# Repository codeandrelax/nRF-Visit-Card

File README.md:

# Bluetooth Compass Project

This project is a personal showcase of my skills in **PCB design, embedded firmware development, and Android application programming**—centered around a custom-built **Bluetooth-enabled digital compass**.

I created this project as a demonstration of my capability to design and manufacture a clean, self-contained PCB solution, free from the reliance on off-the-shelf BLE modules. It’s a manifestation of my passion for building systems from scratch, with a focus on RF design and embedded software.

---

## 🛠️ Hardware Overview

- **Microcontroller**: Nordic nRF52832 with integrated BLE support  
- **Antenna**: Custom-designed **meandering line antenna** tuned to **2.4 GHz**  
- **Magnetometer**: QMC5883L for 3-axis magnetic field sensing (I2C communication)  
- **LEDs**:  
  - 12x Blue LEDs in a circular layout to represent compass directions  
  - 6x Status LEDs: USER, CONNECTIVITY INDICATOR, HEARTBEAT  
- **Battery**: CR2032 coin cell slot  
- **Programming Interface**: SWD (SWCLK, SWDIO), UART connector  
- **Clock**: 32 MHz external crystal for BLE SoftDevice  
- **PCB Stack**: 4-layer custom design, credit-card sized  

> The reset pin is repurposed as a **user input button**. The reset functionality is disabled in software to allow this.

---

## 🔧 Firmware Overview

Firmware is built on **Zephyr RTOS**, enabling modular and modern embedded software design.

A **custom Bluetooth service**, `CompassService`, is implemented, exposing three key characteristics:

1. **Button State**  
2. **User LED Control**  
3. **Direction Output**

### 📡 Magnetometer Integration

- QMC5883L communicates over I2C.  
- Each axis (X, Y, Z) is read as a signed 16-bit value:

```c
int16_t value = (MSB << 8) | LSB;
```

- Orientation is calculated using the X and Y components:

```c
float angle_rad = atan2f((float)mag_y, (float)mag_x);
float angle_deg = angle_rad * (180.0f / M_PI);
if (angle_deg < 0) angle_deg += 360.0f;
```

The direction value is then:
- **Broadcast over BLE** using notify characteristics  
- **Rendered via LEDs** in a circular fashion to act as a real-time compass  

The system runs on the **internal RC oscillator**, while the **external crystal is reserved for BLE operations**.

---

## 📱 Android App Overview

Developed using **Android Studio**, the app uses the **Processing library** to render a dynamic compass needle.

- **BLE scanning** locates the `BluetoothCompass`  
- On connection, the app:  
  - Performs **service discovery**  
  - **Subscribes** to the `Direction` characteristic  
  - **Updates** the compass needle UI in real-time  

This part was relatively straightforward and served as a creative outlet for UI/UX.

---

## 🎯 Purpose

This project was built as a **self-test and demonstration** of:

- Designing an RF-friendly PCB with custom Bluetooth antenna  
- Working with the **nRF52 ecosystem** and BLE stack (SoftDevice + Zephyr)  
- Integrating hardware components like magnetometers and CR2032 power  
- Creating a polished **user-facing Android application**

---

## 🧠 Lessons Learned

Building this project wasn't without hiccups—but every mistake taught me something valuable:

1. **Reversed Magnetometer Pins**  
   Costly PCB error discovered only post-manufacturing. Lesson: Triple-check schematic-to-layout connections.

2. **QFN Soldering Difficulties**  
   My aging soldering iron made soldering QFN packages (magnetometer, MCU) unreliable. Eventually outsourced to **JLCPCB assembly** for these parts.

3. **Signed-to-Unsigned Mistake**  
   I accidentally cast signed 16-bit values from the magnetometer to `uint16_t`, causing direction errors—reminding me of the infamous Ariane 5 bug.

4. **Magnetometer Proximity to Battery**  
   The CR2032 placement near the magnetometer introduced magnetic interference. If I were to redo the board, I’d increase their separation.

5. **No Tilt Compensation**  
   Since the magnetometer acts as a compass only when the board is level, tilts skew the readings. A better design would include an **accelerometer** for tilt compensation:

   ```
   heading = atan2(-Y, X)
   pitch = asin(Z / sqrt(X² + Y² + Z²))
   compensated_heading = heading adjusted for pitch/roll
   ```

---

## 🏁 Conclusion

This project embodies my passion for **electronics**, **firmware engineering**, and **RF system design**. Despite having a **Master’s degree in electronics** and professional experience in embedded development, this personal build was a humbling and rewarding journey. Interestingly, the Android app—which I only work on as a hobby—turned out to be the smoothest part of the whole process!

---

## 🤝 Feedback Welcome!

I enjoy building things I can be proud of—and I’m always open to feedback and suggestions.  
If anything in this project sparks your interest or you’d like to collaborate, feel free to reach out.

## Detailed

This is how it started:

### Schematics

### Layout - bottom copper layer

### Rendered images of the board

### Soldered board

# nRF Connect notes

## How to program the board

[nRF52 DK](https://www.nordicsemi.com/Products/Development-hardware/nRF52-DK) can be used to program the visit card. 

nRF Visit Card board has exposed pads that are used for programming.

### Pinout

## Internal oscilator enable

To enable internal oscilator for nRF52832 in the proj.conf file add:
````
CONFIG_CLOCK_CONTROL_NRF_K32SRC_RC=y
CONFIG_CLOCK_CONTROL_NRF_K32SRC_500PPM=y
CONFIG_CLOCK_CONTROL_NRF_K32SRC_RC_CALIBRATION=y
CONFIG_CLOCK_CONTROL_NRF_CALIBRATION_LF_ALWAYS_ON=y
````

## Enable rest pin to be input GPIO

In the overlay file add:

```
&uicr {
	/delete-property/ gpio-as-nreset;
};
```

after it make sure to call:

```
nrfjprog --eraseuicr
nrfjprog --program <path to hex file> --verify
```

 You might need to reset the board after this - unplug it and plug it back in.

## If _printk_ is not working
In the proj.conf file add:
````
CONFIG_CONSOLE=y
````
## Disabling NFC pins
Pins P0.09 and P0.10 are NFC pins and if you wan't to use them as GPIO pins you need to disable NFC.
[nrf52 enabling gpio on nfc pins](https://devzone.nordicsemi.com/f/nordic-q-a/35505/nrf52-enabling-gpio-on-nfc-pins)
```
CONFIG_NFCT_PINS_AS_GPIOS=y
```

## Enable printing via SWD IO and SWD CLK
In the proj.conf file add:
```
CONFIG_LOG=y
CONFIG_UART_CONSOLE=n
CONFIG_RTT_CONSOLE=y
CONFIG_USE_SEGGER_RTT=y
```
then you can use `printf` function.
```
uint16_t a = getAzimuth();
printf("Azimuth: %d\n", a);
```
Make sure to connect to RTT (Real-Time Transfer).

## 

 # Knowledge Library

 [nRF Connect SDK Fundamentals](https://academy.nordicsemi.com/courses/nrf-connect-sdk-fundamentals/)
 
 [Bluetooth Low Energy Fundamentals](https://academy.nordicsemi.com/courses/bluetooth-low-energy-fundamentals/)

 [Find BLE devices](https://developer.android.com/develop/connectivity/bluetooth/ble/find-ble-devices#java)

 [Processing for Android](https://android.processing.org/tutorials/android_studio/index.html)

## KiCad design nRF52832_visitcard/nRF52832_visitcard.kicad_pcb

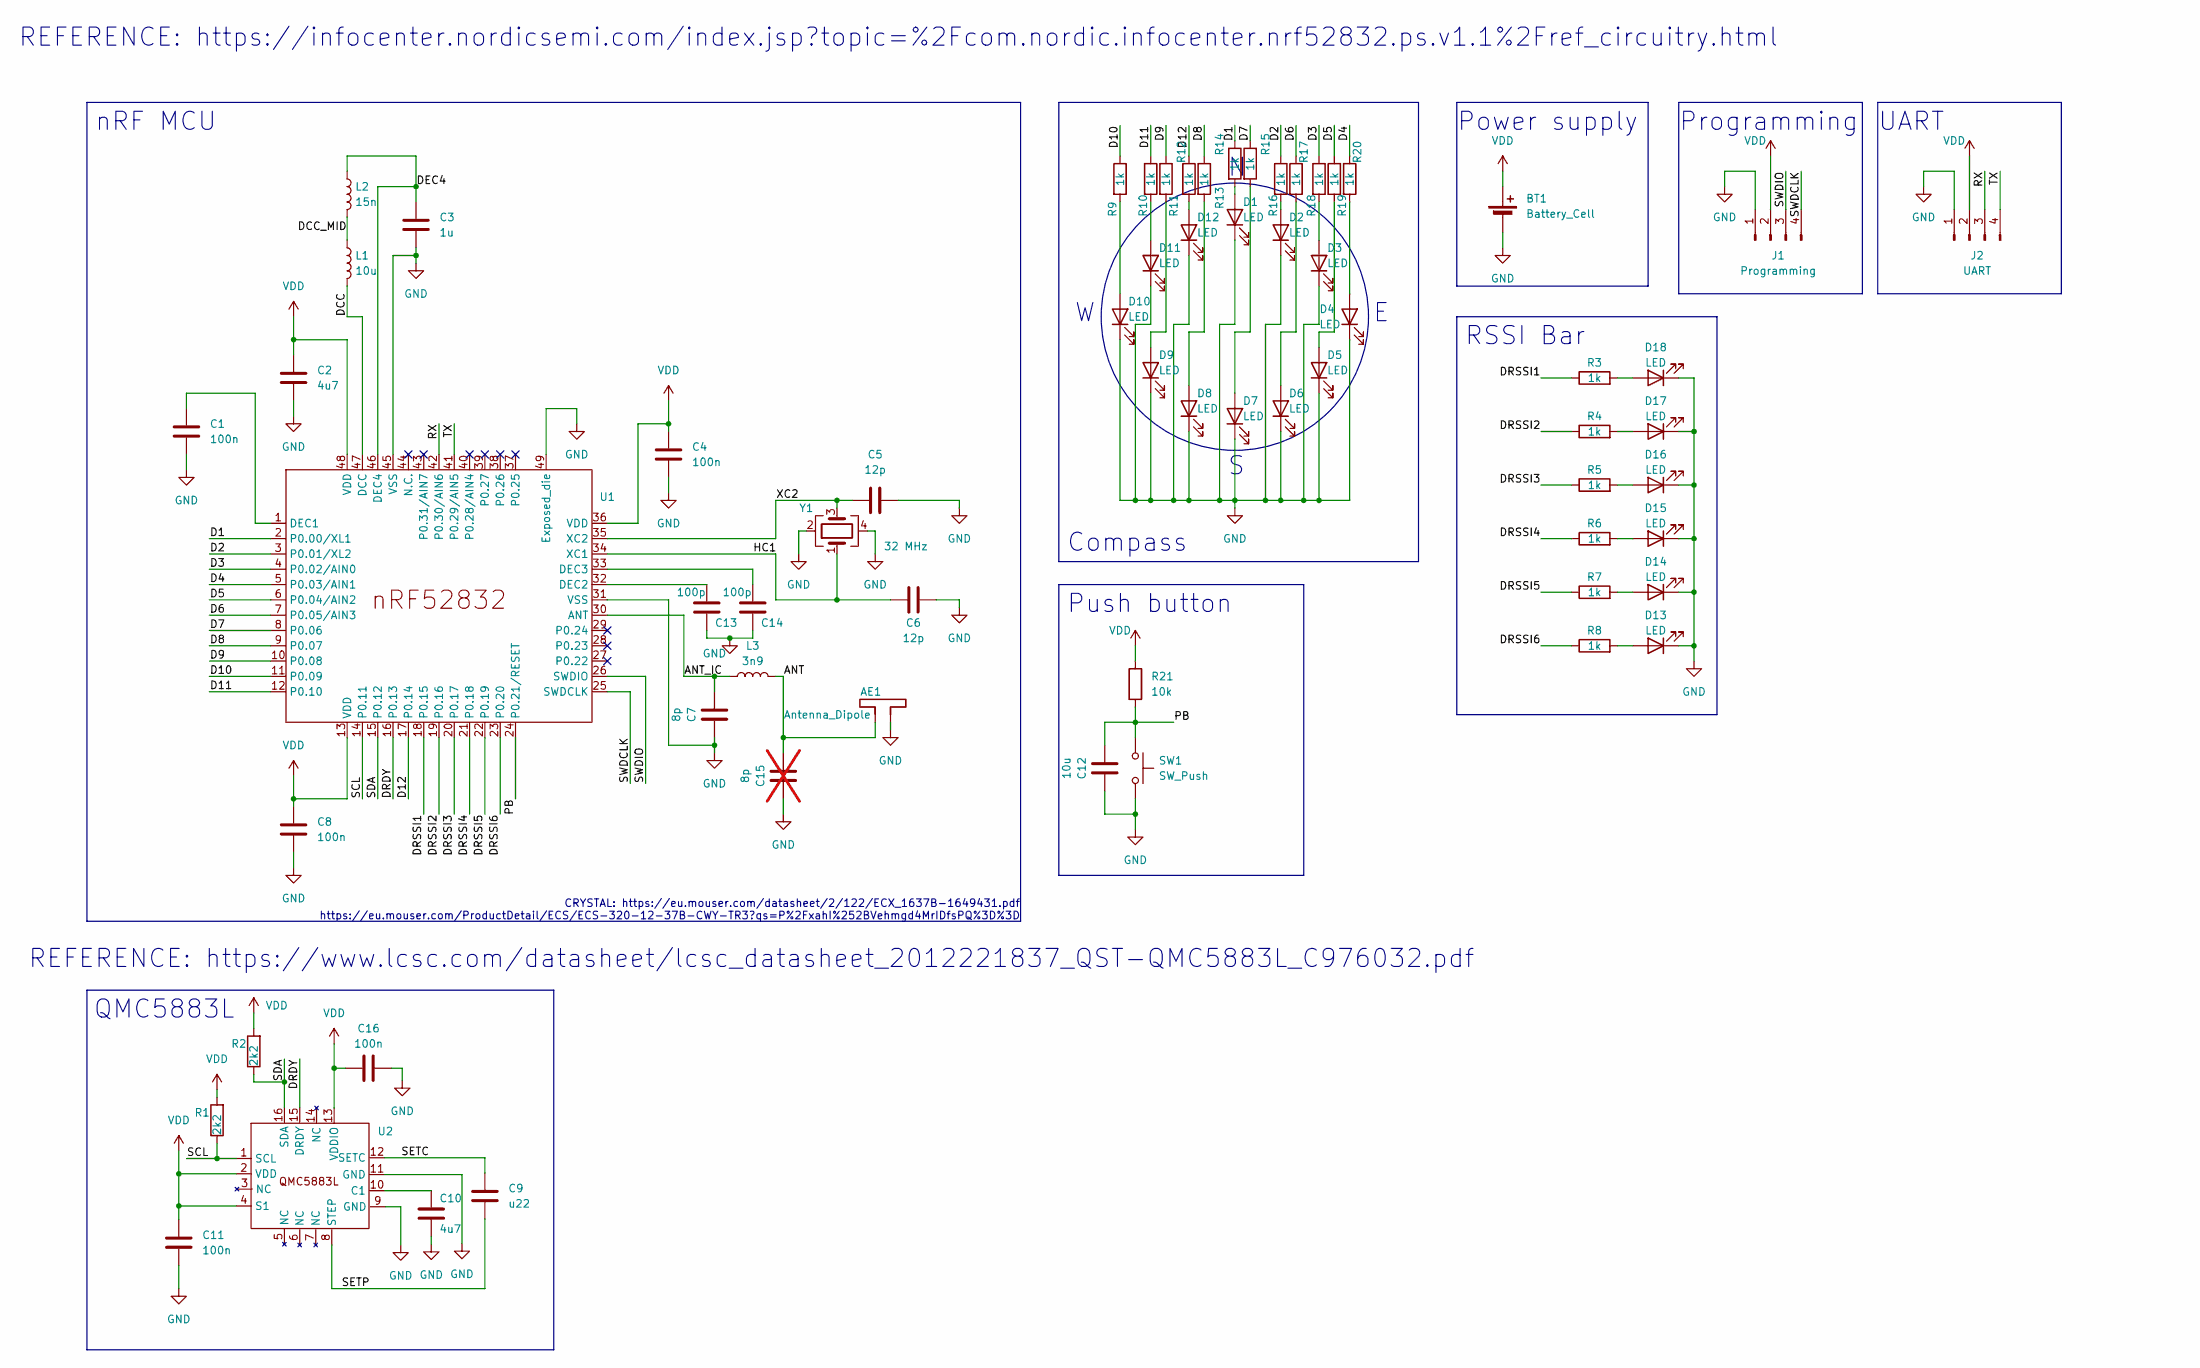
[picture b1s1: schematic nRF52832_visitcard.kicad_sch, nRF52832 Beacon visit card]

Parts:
AE1: Antenna_Dipole; Texas_SWRA117D_2.4GHz_Right
BT1: Battery_Cell; BatteryHolder_Multicomp_BC-2001_1x2032; LCSC C70373
C1, C4, C8: 100n; C_0402_1005Metric_Pad0.74x0.62mm_HandSolder; LCSC C1525
C2: 4u7; C_0603_1608Metric_Pad1.08x0.95mm_HandSolder; LCSC C23687
C3: 1u; C_0603_1608Metric_Pad1.08x0.95mm_HandSolder; LCSC C15684
C5, C6: 12p; C_0402_1005Metric_Pad0.74x0.62mm_HandSolder; LCSC C26406
C7: 8p; C_0402_1005Metric_Pad0.74x0.62mm_HandSolder; LCSC C126516
C9: u22; C_0603_1608Metric_Pad1.08x0.95mm_HandSolder; LCSC C1606
C10: 4u7; C_0603_1608Metric_Pad1.08x0.95mm_HandSolder; LCSC C1705
C11, C16: 100n; C_0805_2012Metric_Pad1.18x1.45mm_HandSolder; LCSC C1711
C12: 10u; C_0603_1608Metric_Pad1.08x0.95mm_HandSolder; LCSC C1691
C13, C14: 100p; C_0402_1005Metric_Pad0.74x0.62mm_HandSolder; LCSC C1546
C15: 8p; C_0402_1005Metric_Pad0.74x0.62mm_HandSolder; not fitted
D1, D2, D3, D4, D5, D6, D7, D8, D9, D10, D11, D12, D13, D14, D15, D16, D17, D18: LED; LED_0603_1608Metric_Pad1.05x0.95mm_HandSolder; LCSC C5197644
J1: Programming; SMD_edgeConnector_4pin
J2: UART; SMD_edgeConnector_4pin
L1: 10u; L_0603_1608Metric_Pad1.05x0.95mm_HandSolder; LCSC C51942
L2: 15n; L_0603_1608Metric_Pad1.05x0.95mm_HandSolder; LCSC C23651
L3: 3n9; L_0603_1608Metric_Pad1.05x0.95mm_HandSolder; LCSC C90202
R1, R2: 2k2; R_0603_1608Metric_Pad0.98x0.95mm_HandSolder; LCSC C25992
R3, R4, R5, R6, R7, R8, R9, R10, R11, R12, R13, R14, R15, R16, R17, R18, R19, R20: 1k; R_0603_1608Metric_Pad0.98x0.95mm_HandSolder; LCSC C14676
R21: 10k; R_0603_1608Metric_Pad0.98x0.95mm_HandSolder; LCSC C15401
SW1: SW_Push; SW_Push_1P1T_NO_6x6mm_H9.5mm; LCSC C499301
U1: QFN-48-1EP_6x6mm_P0.4mm_EP4.6x4.6mm; LCSC C77540
U2: LGA-16_3x3mm_P0.5mm; LCSC C976032
Y1: 32 MHz; Crystal_SMD_2016-4Pin_2.0x1.6mm; LCSC C5830663

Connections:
/ANT: AE1.1, C15.1, L3.2
/ANT_IC: C7.1, L3.1, U1.30 (ANT)
/D1: R14.1, U1.2 (P0.00/XL1)
/D2: R16.1, U1.3 (P0.01/XL2)
/D3: R18.1, U1.4 (P0.02/AIN0)
/D4: R20.1, U1.5 (P0.03/AIN1)
/D5: R19.1, U1.6 (P0.04/AIN2)
/D6: R17.1, U1.7 (P0.05/AIN3)
/D7: R15.1, U1.8 (P0.06)
/D8: R13.1, U1.9 (P0.07)
/D9: R11.1, U1.10 (P0.08)
/D10: R9.1, U1.11 (P0.09)
/D11: R10.1, U1.12 (P0.10)
/D12: R12.1, U1.17 (P0.14)
/DCC: L1.2, U1.47 (DCC)
/DCC_MID: L1.1, L2.2
/DEC4: C3.1, L2.1, U1.46 (DEC4)
/DRDY: U1.16 (P0.13), U2.15 (DRDY)
/DRSSI1: R3.1, U1.18 (P0.15)
/DRSSI2: R4.1, U1.19 (P0.16)
/DRSSI3: R5.1, U1.20 (P0.17)
/DRSSI4: R6.1, U1.21 (P0.18)
/DRSSI5: R7.1, U1.22 (P0.19)
/DRSSI6: R8.1, U1.23 (P0.20)
/HC1: C6.1, U1.34 (XC1), Y1.1
/PB: C12.1, R21.2, SW1.1, U1.24 (P0.21/RESET)
/RX: J2.3, U1.42 (P0.30/AIN6)
/SCL: R1.1, U1.14 (P0.11), U2.1 (SCL)
/SDA: R2.1, U1.15 (P0.12), U2.16 (SDA)
/SETC: C9.1, U2.12 (SETC)
/SETP: C9.2, U2.8 (STEP)
/SWDCLK: J1.4, U1.25 (SWDCLK)
/SWDIO: J1.3, U1.26 (SWDIO)
/TX: J2.4, U1.41 (P0.29/AIN5)
/XC2: C5.1, U1.35 (XC2), Y1.3
GND: AE1.2, BT1.2 (-), C1.2, C2.2, C3.2, C4.2, C5.2, C6.2, C7.2, C8.2, C10.2, C11.2, C12.2, C13.1, C14.1, C15.2, C16.2, D1.1 (K), D2.1 (K), D3.1 (K), D4.1 (K), D5.1 (K), D6.1 (K), D7.1 (K), D8.1 (K), D9.1 (K), D10.1 (K), D11.1 (K), D12.1 (K), D13.1 (K), D14.1 (K), D15.1 (K), D16.1 (K), D17.1 (K), D18.1 (K), J1.1, J2.1, SW1.2, U1.31 (VSS), U1.45 (VSS), U1.49 (Exposed_die), U2.9 (GND), U2.11 (GND), Y1.2, Y1.4
unnamed: D1.2 (A), R14.2
unnamed: D2.2 (A), R16.2
unnamed: D3.2 (A), R18.2
unnamed: D4.2 (A), R20.2
unnamed: D5.2 (A), R19.2
unnamed: D6.2 (A), R17.2
unnamed: D7.2 (A), R15.2
unnamed: D8.2 (A), R13.2
unnamed: D9.2 (A), R11.2
unnamed: D10.2 (A), R9.2
unnamed: D11.2 (A), R10.2
unnamed: D12.2 (A), R12.2
unnamed: D13.2 (A), R8.2
unnamed: D14.2 (A), R7.2
unnamed: D15.2 (A), R6.2
unnamed: D16.2 (A), R5.2
unnamed: D17.2 (A), R4.2
unnamed: D18.2 (A), R3.2
unnamed: C1.1, U1.1 (DEC1)
unnamed: C13.2, U1.32 (DEC2)
unnamed: C14.2, U1.33 (DEC3)
unnamed: C10.1, U2.10 (C1)
VDD: BT1.1 (+), C2.1, C4.1, C8.1, C11.1, C16.1, J1.2, J2.2, R1.2, R2.2, R21.1, U1.13 (VDD), U1.36 (VDD), U1.48 (VDD), U2.2 (VDD), U2.4 (S1), U2.13 (VDDIO)

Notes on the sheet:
Programming
Push button
Power supply
UART
Compass
QMC5883L
RSSI Bar
nRF MCU
REFERENCE: https://www.lcsc.com/datasheet/lcsc_datasheet_2012221837_QST-QMC5883L_C976032.pdf
CRYSTAL: https://eu.mouser.com/datasheet/2/122/ECX_1637B-1649431.pdf https://eu.mouser.com/ProductDetail/ECS/ECS-320-12-37B-CWY-TR3?qs=P%2FxahI%252BVehmgd4MrIDfsPQ%3D%3D
REFERENCE: https://infocenter.nordicsemi.com/index.jsp?topic=%2Fcom.nordic.infocenter.nrf52832.ps.v1.1%2Fref_circuitry.html

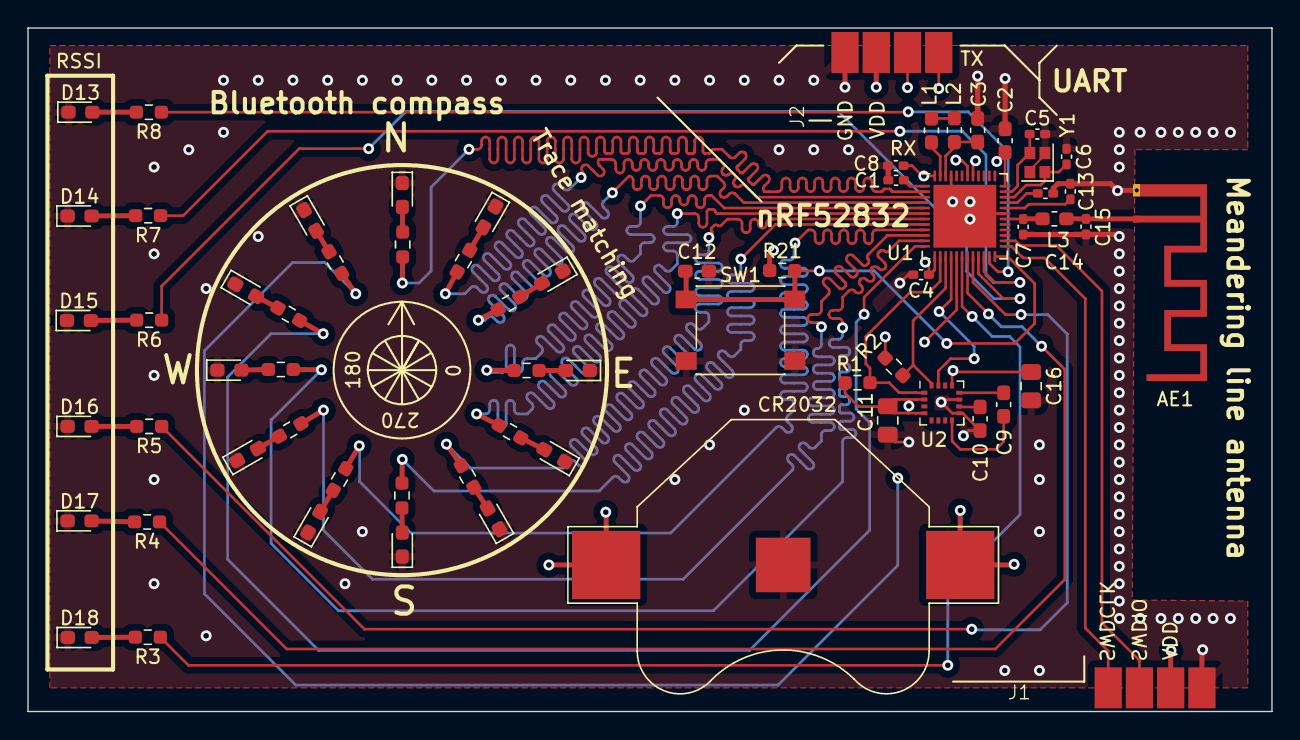
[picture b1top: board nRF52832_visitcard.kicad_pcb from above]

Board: 4 copper layers, 91.0 x 50.0 mm, 67 parts (1 on the bottom side), 59 nets.

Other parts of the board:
 : Gauge_50mm_Type1_SilkScreenTop

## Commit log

2024-09-19 PCB Visit Card first push
2024-09-19 3D models to PCB added
2024-09-26 Magnetometer reading
2024-10-01 Concept block diagram added
2024-10-07 Firmware functionality diagram
2024-11-21 Generating BOM
2024-11-22 Added LCSC to all the components
2024-11-22 LCSC added to another component
2024-11-24 Board layout fix
2024-12-04 Using QMC5833L instead of HMC5883L
2025-04-19 Android software development
2025-04-19 Removal of old files
2025-04-19 Removal of DS_Store file
2025-04-28 PCB details - Rotated battery holder in 3D view - Silkscreen fix
2025-04-28 Firmawre: - Added firware - Added custom device tree source for bluetooth compass
